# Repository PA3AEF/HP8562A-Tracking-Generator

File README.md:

# Tracking Generator for the HP 8562A/B Spectrum Analyzer  
**Reconstructing the Analyzer’s RF Sweep from Its Local Oscillator**  
**A modular, analyzer‑synchronous architecture**

PA3AEF 2026 

## What this project is

The HP 8562A/B spectrum analyzer does not include a tracking generator.  
However, it exposes enough of its internal LO system to build one externally.

This project implements a **modular, sweep‑synchronous Tracking Generator (TG)** that behaves as if it were a native part of the HP 8562A/B.  
It reconstructs the analyzer’s RF sweep using only:

- 1st LO Output (about 3.9–6.8 GHz)  
- LO Sweep Output (0–10 V, 0.5 V/GHz)  
- 10 MHz reference

The TG becomes a slave to the analyzer’s LO system and rebuilds the RF sweep in real time across multiple microwave bands.

## Why build a Tracking Generator for the HP 8562A/B?

The HP 8562A/B is a legendary instrument: fast, sensitive, and extremely stable.  
But without a tracking generator, it cannot perform:

- filter alignment  
- cavity tuning  
- antenna measurements  
- scalar network analysis  
- frequency response characterization  

This project fills that gap with a TG that follows the analyzer sweep exactly, using the analyzer’s own LO architecture.

## How the analyzer sweeps — and how the TG reconstructs the RF

The HP 8562A/B does not sweep an RF source.  
It sweeps its **first local oscillator** and mixes incoming signals down to a fixed IF.  
To cover 1 kHz–26 GHz, it uses **automatic harmonic mixing**, where each RF band uses a different harmonic of the LO:

| RF Band | Harmonic n | IF | LO Formula |
|--------:|:----------:|----------:|-----------|
| 1 kHz–2.9 GHz | 1 | 3.9107 GHz | LO_SA = RF_SA + 3.9107 GHz |
| 2.75–6.46 GHz | 1 | 310.7 MHz | LO_SA = RF_SA + 0.3107 GHz |
| 5.86–13.0 GHz | 2 | 310.7 MHz | LO_SA = (RF_SA + 0.3107 GHz) / 2 |
| 12.4–19.7 GHz | 3 | 310.7 MHz | LO_SA = (RF_SA + 0.3107 GHz) / 3 |
| 19.1–26.0 GHz | 4 | 310.7 MHz | LO_SA = (RF_SA + 0.3107 GHz) / 4 |

For each band, the analyzer follows: `n * LO_SA = RF_SA + IF`

Because **n changes with band**, the analyzer LO becomes **non‑linear** with respect to the displayed frequency.

A tracking generator must compensate for this non‑linearity to stay aligned.

## How the TG reconstructs the analyzer RF

The TG uses the analyzer LO_SA (or a harmonic of it) as the primary LO and subtracts a fixed IF to recreate the analyzer’s RF:

```
RF_TG = (n * LO_SA) – IF_TG
```

Where:

- IF_TG = 310.7 MHz (fixed for all microwave TG modules)  
- n = analyzer harmonic mode for that band  

This yields:

- Base‑Band (n = 1):  
  RF_TG = LO_SA – 3.9107 GHz

- 6 cm (n = 1):  
  RF_TG = LO_SA – 0.3107 GHz

- 3 cm (n = 2):  
  RF_TG = (2 × LO_SA) – 0.3107 GHz

- 12 mm (n = 4, concept):  
  RF_TG = (4 × LO_SA) – 0.3107 GHz

This architecture reqires **no swept PLLs** in the microwave TG modules.  
Sweep coherence comes entirely from the analyzer LO.

## High‑level TG architecture

The TG system is composed of modular RF boards:

- **MCU board:**  
  Reads sweep voltage, computes RF_SA for calibration, programs PLLs

- **RF SA‑LO Distribution board:**  
  Conditions and splits the analyzer’s 1st LO to all TG modules

- **Base‑Band TG module:**  
  0–2.9 GHz (uses MAX2870)

- **6 cm TG module:**  
  4.4–6.4 GHz (LO_SA direct, IF_TG = 310.7 MHz)

- **3 cm TG module:**  
  9.5–11.5 GHz (LO_SA ×2, IF_TG = 310.7 MHz)

- **12 mm TG module (concept):**  
  22–26 GHz (LO_SA ×4, IF_TG = 310.7 MHz)

Conceptually:

```
Analyzer → LO Distribution → TG Modules → RF Outputs
Analyzer → 10 MHz → PLLs
Analyzer → V_sweep → MCU → Harmonic modules
```

Each TG module reconstructs the analyzer RF at its own band using a mixer‑based architecture.

## TG coverage limits

- **Implemented TG bands:**  
  - Base‑Band (0–2.9 GHz)  
  - 6 cm (4.4–6.4 GHz)  
  - 3 cm (9.5–11.5 GHz)

- **Conceptual / future TG bands:**  
  - 12 mm (22–26 GHz)

- **Analyzer coverage:**  
  - Up to 26 GHz with Option 026  
  - TG coverage currently ends at 11.5 GHz

## Repository structure

```
/docs/architecture
    01-tg-system-architecture.md
    02-lo-architecture.md
    03-analyser-lo-internals.md
    04-rf-sa-lo-distribution.md
    05-baseband-module.md
    06-6cm-module.md
    07-3cm-module.md
    08-12mm-module.md
/docs/architecture/images
    architecture diagrams
/firmware
    MCU firmware (Raspberry Pi Pico)
    overview
    images
/hardware/<module>
    schematics, layouts, BOMs, images
/mechanical
    enclosures, front panels
/usage
    calibration and measurement tools
```

## Status (Oct 19, 2026)

Checkout the [discussion section](https://github.com/PA3AEF/HP8562A-Tracking-Generator/discussions) for updates on the first results I have. 

- File: [example S21 3 cm lossy filter](./images/s21-3cm-lossy-filter.jpg)
- File: [example S11 3 cm pole filter](./images/s11-3cm-pole-filter.jpg)
- MCU board: finshed (I have some boards available) 
- Firmware: finished (Base-band, 6cm and 3cm) 
- LO Distribution: finished 
- Base‑Band module: finished  
- 3 cm module: proof of concept tested OK (tracking at 10 GHz with 2 GHz span)  
- 6 cm module: architecture defined  
- 12 mm module: conceptual design complete  

## License

MIT License.  
See `LICENSE` for details.

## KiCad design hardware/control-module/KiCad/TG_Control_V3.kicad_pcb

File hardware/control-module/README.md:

# Control Module — MCU and 10 MHz Reference Buffer (Hardware)

Compact hardware overview for the Control Module: power sequencing, protection, MCU host interfaces, and the low‑noise 10 MHz reference buffering and 1:4 distribution. Detailed hardware-level descriptions for the **10 MHz reference** and **MCU** are in separate documents (`docs/10MHz_reference.md`, `docs/mcu-hardware.md`). Firmware is covered elsewhere.

## Purpose

- Buffer and distribute an external **10 MHz reference** to **4 isolated outputs**  
- Provide MCU-host hardware: power, programming, debug, and physical control interfaces  
- Protect and condition reference and power inputs (ESD, TVS, reverse polarity)  
- Present SPI/UART/USB headers and status indicators for system integration

## Block Diagram

10 MHz Ref In → Input Protection → Low‑noise Buffer → 1:4 Splitter/Switch → Output Buffers → **4 × SMA REF OUT**  
Power In → Sequencing & Regulators → MCU + Peripherals  
MCU headers: SPI, UART, VRef, Switch, RF-Modules

## Hardware Interfaces

- **Reference Input**
  - **SMA** connector with input protection and level detect
  - DC blocking and optional AC coupling upstream of buffer
- **Reference Outputs**
  - **4 × SMA** buffered outputs, individually enabled
  - Target nominal level: **0 dBm** per output (see `docs/10MHz_reference.md`)
- **Control / Comms**
  - **SPI** header (MOSI, MISO, SCLK, CS, GND, Vcc) for downstream PLLs
  - **UART / USB** hardware interface for firmware connectivity
- **Power**
  - External DC input with reverse‑polarity protection
  - Onboard regulators with power‑good signals and sequencing
- **Indicators**
  - Power, module-select and lock detect fault LEDs at PCB headers

## Design Notes (Hardware Only)

- **Phase noise:** buffer chosen to add minimal phase noise; layout keeps RF ground continuous under RF chain.  
- **Isolation:** per‑output buffering prevents cross‑talk; outputs terminated and DC‑blocked.  
- **Protection:** input ESD, TVS, and surge protection on REF IN and power rails.  
- **Mechanical:** SMA connectors on PCB edge; keep digital switching components physically separated from RF path.  
- **EMC:** ferrite beads, common‑mode chokes, and local decoupling to reduce digital noise coupling into 10 MHz path.  
- **Test points:** RF amplitude, buffer bias, and power‑good nets exposed for bench verification.

## Connector / Pin Summary

- **REF IN:** SMA (10 MHz)  
- **REF OUT 1–4:** SMA buffered outputs  
- **SPI:** 6‑pin header (MOSI, MISO, SCLK, CS, GND, Vcc)  
- **UART/USB:** Micro‑USB or TTL UART header  
- **POWER:** Screw terminal or header;
- **Band Selection:** 3-pin header
- **LO Switch:** 3-pin header
- **RF Modules:** 3-pin and 2-pin headers 

## Control Module

## Documentation

Hardware detail references:  
- **`10MHz_reference.md`** — full schematic, BOM, and RF measurements  
- **`mcu-hardware.md`** — MCU pinout, power sequencing, and debug connectors  
- **`control-module`** — mechanical drawings and test fixtures

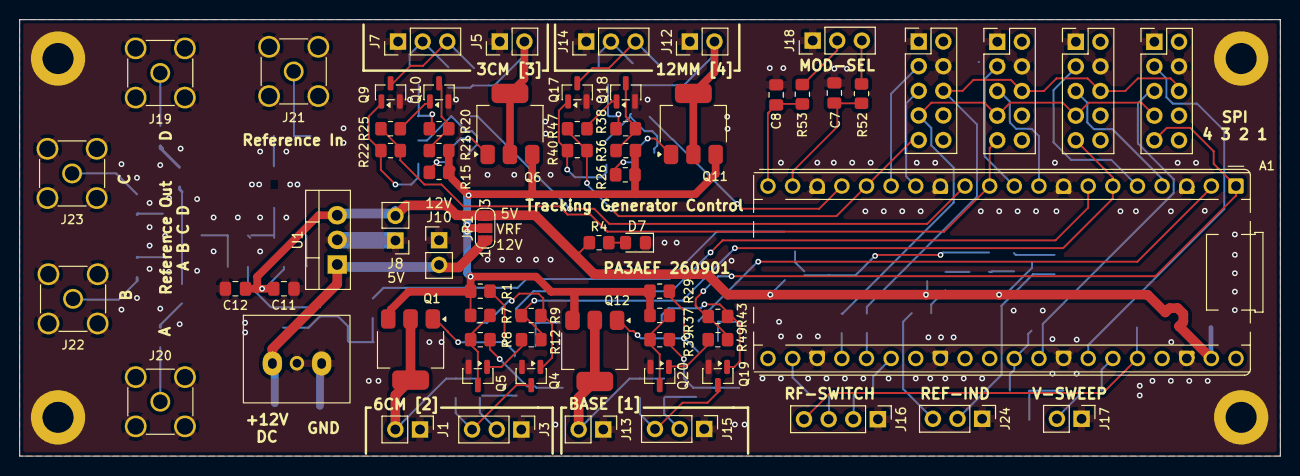
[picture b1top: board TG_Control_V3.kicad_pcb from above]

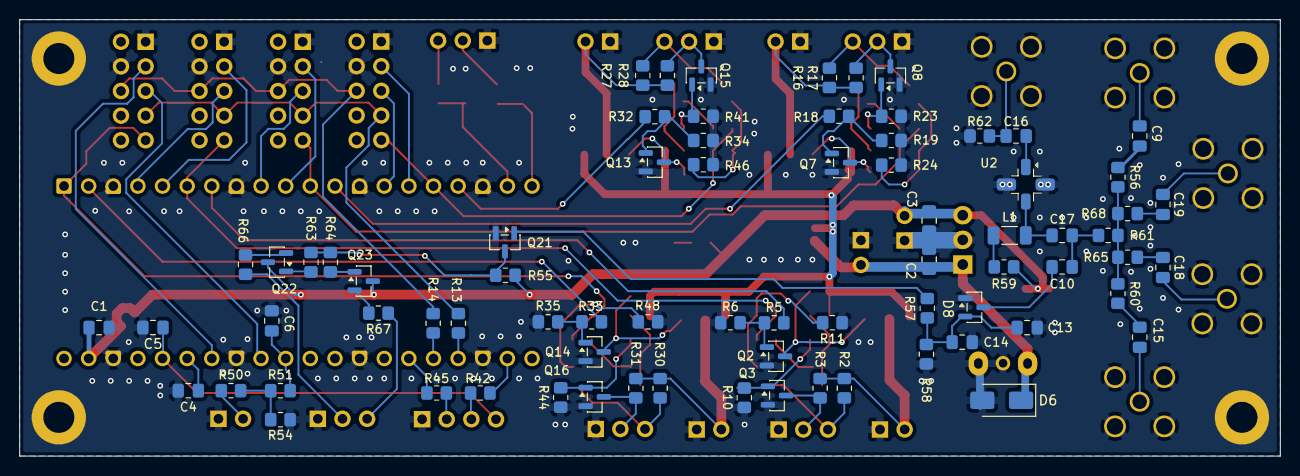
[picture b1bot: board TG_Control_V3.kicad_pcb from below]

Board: 2 copper layers, 130.0 x 45.0 mm, 146 parts (75 on the bottom side), 98 nets.

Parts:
A1: RaspberryPi_Pico; RaspberryPi_Pico_Common_THT
C1, C3, C4, C5, C6, C7, C8, C9, C11, C15, C16, C17, C18, C19: 100nF; C_0805_2012Metric_Pad1.18x1.45mm_HandSolder
C2: 330nF; C_0805_2012Metric_Pad1.18x1.45mm_HandSolder
C10: 1pF; C_0805_2012Metric_Pad1.18x1.45mm_HandSolder
C12: 10uF; C_0805_2012Metric_Pad1.18x1.45mm_HandSolder
C13: 1nF; C_0805_2012Metric_Pad1.18x1.45mm_HandSolder
C14: 47uF; C_0805_2012Metric_Pad1.18x1.45mm_HandSolder
D6: 1N4001; D_SMA
D7: LED; LED_0805_2012Metric_Pad1.15x1.40mm_HandSolder
D8: BAT54S; SOT-23
H1, H2, H3, H4: MountingHole_Pad; MountingHole_3.2mm_M3_DIN965_Pad
J1, J5, J8, J10, J12, J13, J17: Conn_01x02; PinHeader_1x02_P2.54mm_Vertical
J2: SCREW_TERMINAL; Screw terminal 3 pin
J3, J7, J14, J15, J18, J24: Conn_01x03; PinHeader_1x03_P2.54mm_Vertical
J4, J6, J9, J11: Conn_02x05_Odd_Even; PinHeader_2x05_P2.54mm_Vertical
J16: Conn_01x04; PinHeader_1x04_P2.54mm_Vertical
J19, J20, J21, J22, J23: Conn_Coaxial; SMA_Amphenol_901-144_Vertical
JP1: SolderJumper_3_Open; SolderJumper-3_P1.3mm_Open_RoundedPad1.0x1.5mm_NumberLabels
L1: 22nH; L_1206_3216Metric_Pad1.22x1.90mm_HandSolder
Q1, Q6, Q11, Q12: ZXMP4A16G; SOT-223-3_TabPin2
Q2, Q3, Q4, Q5, Q7, Q8, Q9, Q10, Q13, Q14, Q15, Q16, Q17, Q18, Q19, Q20, Q23: MMBTA14; SOT-23
Q21: MMBT3904; SOT-23
Q22: BC857; SOT-23
R1, R5, R8, R9, R12, R15, R18, R21, R22, R25, R26, R29, R32, R33, R38, R39, R40, R43, R47, R49, R54, R63, R64: 10K; R_0805_2012Metric_Pad1.20x1.40mm_HandSolder
R2, R3, R16, R17, R27, R28, R30, R31: **; R_0805_2012Metric_Pad1.20x1.40mm_HandSolder
R4, R66, R67: 3K3; R_0805_2012Metric_Pad1.20x1.40mm_HandSolder
R6, R10, R11, R19, R23, R24, R34, R35, R41, R44, R46, R48: 100K; R_0805_2012Metric_Pad1.20x1.40mm_HandSolder
R7, R20, R36, R37: 68K; R_0805_2012Metric_Pad1.20x1.40mm_HandSolder
R13, R14: 0R; R_0805_2012Metric_Pad1.20x1.40mm_HandSolder
R42, R45, R52, R53: 100R; R_0805_2012Metric_Pad1.20x1.40mm_HandSolder
R50: 22K; R_0805_2012Metric_Pad1.20x1.40mm_HandSolder
R51: 1K; R_0805_2012Metric_Pad1.20x1.40mm_HandSolder
R55: 3k3; R_0805_2012Metric_Pad1.20x1.40mm_HandSolder
R56, R60, R61, R65, R68: 39R; R_0805_2012Metric_Pad1.20x1.40mm_HandSolder
R57: 8k2; R_0805_2012Metric_Pad1.20x1.40mm_HandSolder
R58: 47K; R_0805_2012Metric_Pad1.20x1.40mm_HandSolder
R59: 33R; R_0805_2012Metric_Pad1.20x1.40mm_HandSolder
R62: 49R9; R_0805_2012Metric_Pad1.20x1.40mm_HandSolder
U1: LM7805_TO220; TO-220-3_Vertical
U2: MAR-6+; MSA_1

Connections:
+3V3: A1.36 (3V3), C5.1, J16.4
+5V: A1.39 (VSYS), C1.2, C3.1, C11.2, C12.2, J8.2, JP1.3 (B), Q22.3 (C), Q23.3 (C), R4.1, R55.1, R59.2, U1.3 (VO)
+12V: C2.1, D6.1 (K), J2.1, J10.2, JP1.1 (A), U1.1 (VI)
/10 MHz Reference/REF-DETECT: J24.2, R66.2
/10 MHz Reference/REF-DETECT-N: J24.3, R67.1
/10 MHz Reference/REF_DET_N: Q21.3 (C), R55.2, R63.1, R64.1
/10 MHz Reference/REF_PRESENT: C10.1, C17.2, R61.1
/MCU/CE_3CM: A1.10 (GPIO7), J9.3
/MCU/CE_6CM: A1.5 (GPIO3), J6.3
/MCU/CE_12MM: A1.15 (GPIO11), J11.3
/MCU/CE_BASE: A1.34 (GPIO28_ADC2), J4.3
/MCU/CS_3CM: A1.9 (GPIO6), J9.5
/MCU/CS_6CM: A1.4 (GPIO2), J6.5
/MCU/CS_12MM: A1.14 (GPIO10), J11.5
/MCU/CS_BASE: A1.32 (GPIO27_ADC1), J4.5
/MCU/LD-3CM-GN: J7.2, Q8.3 (C), R17.2
/MCU/LD-3CM-RD: J7.3, Q9.3 (C), R16.1
/MCU/LD-6CM-GN: J3.2, Q3.3 (C), R3.2
/MCU/LD-6CM-RD: J3.3, Q4.3 (C), R2.1
/MCU/LD-12MM-GN: J14.2, Q15.3 (C), R28.2
/MCU/LD-12MM-RD: J14.3, Q17.3 (C), R27.1
/MCU/LD-BASE-GN: J15.2, Q16.3 (C), R31.2
/MCU/LD-BASE-RD: J15.3, Q19.3 (C), R30.1
/MCU/LD_3CM: A1.11 (GPIO8), J9.9, R22.1, R25.1
/MCU/LD_6CM: A1.6 (GPIO4), J6.9, R9.1, R12.1
/MCU/LD_12MM: A1.16 (GPIO12), J11.9, R40.1, R47.1
/MCU/LD_BASE: A1.1 (GPIO0), J4.9, R43.1, R49.2
/MCU/MOD-SEL1: J18.2, R53.1
/MCU/MOD-SEL2: J18.3, R52.1
/MCU/MOSI: J4.6, J6.6, J9.6, J11.6, R14.2
/MCU/PE_A: A1.26 (GPIO20), R45.2
/MCU/PE_B: A1.22 (GPIO17), R42.2
/MCU/RF-3CM-PWR: J5.2, Q6.2 (D), R16.2, R17.1
/MCU/RF-6CM-PWR: J1.2, Q1.2 (D), R2.2, R3.1
/MCU/RF-12MM-PWR: J12.2, Q11.2 (D), R27.2, R28.1
/MCU/RF-BASE-PWR: J13.2, Q12.2 (D), R30.2, R31.1
/MCU/RFEN_3CM: A1.12 (GPIO9), R18.1
/MCU/RFEN_6CM: A1.7 (GPIO5), R5.1
/MCU/RFEN_12MM: A1.17 (GPIO13), R32.1
/MCU/RFEN_BASE: A1.2 (GPIO1), R33.1
/MCU/RFSW-A: J16.2, R45.1
/MCU/RFSW-B: J16.3, R42.1
/MCU/ROT_A: A1.19 (GPIO14), C7.1, R52.2
/MCU/ROT_B: A1.20 (GPIO15), C8.1, R53.2
/MCU/SCK: J4.7, J6.7, J9.7, J11.7, R13.2
/MCU/V_RF: JP1.2 (C), Q1.3 (S), Q6.3 (S), Q11.3 (S), Q12.3 (S), R1.1, R7.2, R15.1, R20.2, R26.1, R29.1, R36.2, R37.2
/MCU/Vsense: A1.31 (GPIO26_ADC0), C6.1, R51.2
GND: A1.3 (GND), A1.8 (GND), A1.13 (GND), A1.18 (GND), A1.23 (GND), A1.28 (GND), A1.33 (AGND), A1.38 (GND), C1.1, C2.2, C3.2, C4.2, C5.2, C6.2, C7.2, C8.2, C11.1, C12.1, C13.1, C14.1, D6.2 (A), D7.1 (K), D8.1 (A), H1.1 (1_1), H2.1 (1_1), H3.1 (1_1), H4.1 (1_1), J1.1, J2.2, J3.1, J4.1, J4.4, J5.1, J6.1, J6.4, J7.1, J8.1, J9.1, J9.4, J10.1, J11.1, J11.4, J12.1, J13.1, J14.1, J15.1, J16.1, J17.1, J18.1, J19.2 (Ext), J20.2 (Ext), J21.2 (Ext), J22.2 (Ext), J23.2 (Ext), J24.1, Q2.2 (E), Q3.2 (E), Q4.2 (E), Q5.2 (E), Q7.2 (E), Q8.2 (E), Q9.2 (E), Q10.2 (E), Q13.2 (E), Q14.2 (E), Q15.2 (E), Q16.2 (E), Q17.2 (E), Q18.2 (E), Q19.2 (E), Q20.2 (E), Q21.2 (E), R6.1, R10.1, R11.1, R19.1, R23.1, R24.1, R34.1, R35.1, R41.1, R44.1, R46.1, R48.1, R54.2, R58.2, R62.2, U1.2 (GND), U2.3 (GND), U2.4 (GND)
unnamed: A1.35 (ADC_VREF), C4.1
unnamed: A1.24 (GPIO18), R13.1
unnamed: A1.25 (GPIO19), R14.1
unnamed: C9.1, R56.2
unnamed: C15.1, R60.2
unnamed: C18.1, R65.2
unnamed: C19.1, R68.2
unnamed: D7.2 (A), R4.2
unnamed: C10.2, D8.3 (COM)
unnamed: C13.2, C14.2, D8.2 (K), R57.1, R58.1
unnamed: J17.2, R50.1
unnamed: C9.2, J19.1 (In)
unnamed: C15.2, J20.1 (In)
unnamed: C16.1, J21.1 (In), R62.1
unnamed: C18.2, J22.1 (In)
unnamed: C19.2, J23.1 (In)
unnamed: L1.1, R59.1
unnamed: Q1.1 (G), Q2.3 (C), R1.2
unnamed: Q2.1 (B), R5.2, R6.2
unnamed: Q3.1 (B), R8.2, R10.2
unnamed: Q4.1 (B), R9.2, R11.2
unnamed: Q5.1 (B), R12.2
unnamed: Q5.3 (C), R7.1, R8.1
unnamed: Q6.1 (G), Q7.3 (C), R15.2
unnamed: Q7.1 (B), R18.2, R19.2
unnamed: Q8.1 (B), R21.2, R23.2
unnamed: Q9.1 (B), R22.2, R24.2
unnamed: Q10.1 (B), R25.2
unnamed: Q10.3 (C), R20.1, R21.1
unnamed: Q11.1 (G), Q13.3 (C), R26.2
unnamed: Q12.1 (G), Q14.3 (C), R29.2
unnamed: Q13.1 (B), R32.2, R34.2
unnamed: Q14.1 (B), R33.2, R35.2
unnamed: Q15.1 (B), R38.2, R41.2
unnamed: Q16.1 (B), R39.2, R44.2
unnamed: Q17.1 (B), R40.2, R46.2
unnamed: Q18.1 (B), R47.2
unnamed: Q18.3 (C), R36.1, R38.1
unnamed: Q19.1 (B), R43.2, R48.2
unnamed: Q20.1 (B), R49.1
unnamed: Q20.3 (C), R37.1, R39.1
unnamed: Q21.1 (B), R57.2
unnamed: Q22.1 (B), R63.2
unnamed: Q22.2 (E), R66.1
unnamed: Q23.1 (B), R64.2
unnamed: Q23.2 (E), R67.2
unnamed: R50.2, R51.1, R54.1
unnamed: R56.1, R60.1, R61.2, R65.1, R68.1
unnamed: C16.2, U2.1 (IN)
unnamed: C17.1, L1.2, U2.2 (OUT)

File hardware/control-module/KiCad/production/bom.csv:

Designator,Footprint,Quantity,Value,LCSC Part #
A1,RaspberryPi_Pico_Common_THT,1,RaspberryPi_Pico,
"C1, C11, C15, C16, C17, C18, C19, C3, C4, C5, C6, C7, C8, C9",0805,14,100nF,
C10,0805,1,1pF,
C12,0805,1,10uF,
C13,0805,1,1nF,
C14,0805,1,47uF,
C2,0805,1,330nF,
D6,D_SMA,1,1N4001,
D7,0805,1,LED,
D8,SOT-23,1,BAT54S,
"J1, J10, J12, J13, J5, J8",PinHeader_1x02_P2.54mm_Vertical,6,Conn_01x02,
"J11, J4, J6, J9",PinHeader_2x05_P2.54mm_Vertical,4,Conn_02x05_Odd_Even,
"J14, J15, J18, J24, J3, J7",PinHeader_1x03_P2.54mm_Vertical,6,Conn_01x03,
J16,PinHeader_1x04_P2.54mm_Vertical,1,Conn_01x04,
"J19, J20, J21, J22, J23",SMA_Amphenol_901-144_Vertical,5,Conn_Coaxial,
J2,Screw terminal 3 pin,1,SCREW_TERMINAL,
L1,1206,1,22nH,
"Q1, Q11, Q12, Q6",SOT-223-3_TabPin2,4,ZXMP4A16G,
"Q10, Q13, Q14, Q15, Q16, Q17, Q18, Q19, Q2, Q20, Q23, Q3, Q4, Q5, Q7, Q8, Q9",SOT-23,17,MMBTA14,
Q21,SOT-23,1,MMBT3904,
Q22,SOT-23,1,BC857,
"R1, R12, R15, R18, R21, R22, R25, R26, R29, R32, R33, R38, R39, R40, R43, R47, R49, R5, R63, R64, R8, R9",0805,22,10K,
"R10, R11, R19, R23, R24, R34, R35, R41, R44, R46, R48, R6",0805,12,100K,
"R13, R14",0805,2,0R,
"R16, R17, R2, R27, R28, R3, R30, R31",0805,8,**,
"R20, R36, R37, R7",0805,4,68K,
"R4, R55, R66, R67",0805,4,3K3,
"R42, R45, R52, R53",0805,4,100R,
"R56, R60, R61, R65, R68",0805,5,39R,
R57,0805,1,8k2,
R58,0805,1,47K,
R59,0805,1,33R,
R62,0805,1,49R9,
U1,TO-220-3_Vertical,1,LM7805_TO220,
U2,MSA_1,1,MAR-6+,

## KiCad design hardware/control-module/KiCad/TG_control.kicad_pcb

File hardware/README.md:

# Hardware — TG Project

This directory contains all hardware designs for the modular Tracking Generator (TG).  
Each RF module is fully self‑contained with its own schematic, PCB if applicable, and data on on read-made building-blocks.

The hardware is organized into four primary modules:

- **Baseband Module (0–2.9 GHz)**
- **6 cm Module (4.4–6.4 GHz)**
- **3 cm Module (8.5–11.5 GHz)**
- **LO Module (Isolation and distribution of 1st LO from SA)**

All PCBs are designed in KiCad and stored in separate subdirectories.

## Directory Structure

Each module directory contains:

- **`schematic.pdf`** — complete schematic  
- **`pcb/`** — KiCad PCB files, 3D views, fabrication output  
- **`bom.csv`** — Bill of Materials  
- **`readme.md`** — module‑specific documentation (gain budget, design notes, test plan)

## Hardware Module Overview

### **Baseband Module (0–2.9 GHz)**
- IF chain from the HMC219 downconverter
- PLL at 3.9107 GHz  
- 3 GHz low‑pass filter  
- Pads, IF amplifier, SMA output  

### **6 cm Module (4.4–6.4 GHz)**
- HMC220 mixer  
- IF and RF amplification  
- Band‑pass filtering for 4–8 GHz  
- Purpose: upconversion for the 6 cm tracking generator band

### **3 cm Module (9.5–11.5 GHz)**
- HMC220 mixer 
- PLL at 310.7 MHz
- Band-pass filter at 310 MHz 
- High‑frequency RF amplifier (9–12 GHz)  
- Band‑pass filtering for 8–12 GHz  
- Purpose: upconversion for the 3 cm tracking generator band

### **Control Module**
- Raspberry Pi microcontroller
- Control of all circuitry, indicators, etc.
- Power provision for each band module (5-12V selectable) 
- Prper startup-shutdown sequence for band switching
- 10 MHz reference input buffering and distribution (SMA)
- SPI control for PLLs 

### **LO Module**
- Isolation of 1st LO output of analyser
- Braodband amplification of 1st LO output
- Distribution of 1st LO to band modules 

## Design Principles

- **Modular:** each RF module is electrically and mechanically independent  
- **SMA‑based:** all interconnects use SMA cables for clean, predictable RF paths  
- **Reproducible:** BOMs, schematics, and PCB files are fully documented  
- **RF‑optimized:** short signal paths, solid grounding, controlled impedance  
- **Measurable:** each module includes clear test points and a documented gain budget

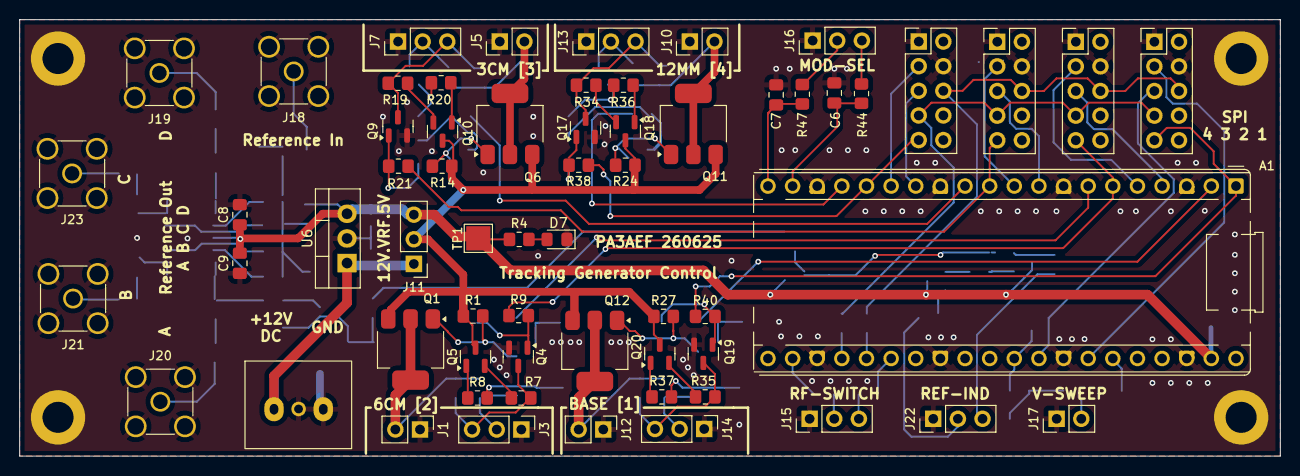
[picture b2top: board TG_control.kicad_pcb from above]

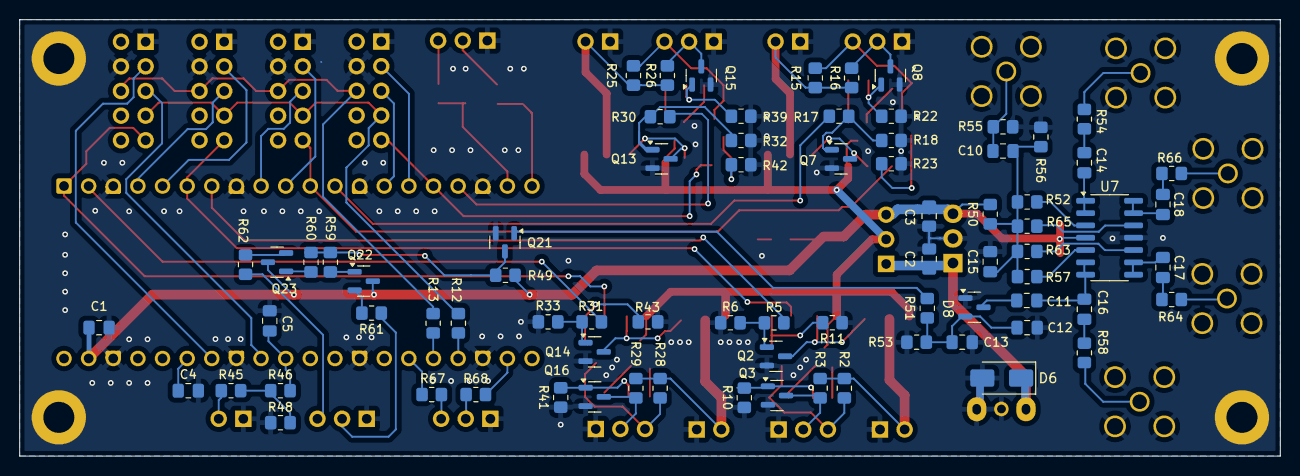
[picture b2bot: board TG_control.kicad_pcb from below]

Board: 2 copper layers, 130.0 x 45.0 mm, 143 parts (77 on the bottom side), 101 nets.

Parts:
A1: RaspberryPi_Pico; RaspberryPi_Pico_Common_THT
C1, C3, C4, C5, C6, C7, C9, C10, C14, C16, C17, C18: 100nF; C_0805_2012Metric_Pad1.18x1.45mm_HandSolder
C2: 330nF; C_0805_2012Metric_Pad1.18x1.45mm_HandSolder
C8: 10uF; C_0805_2012Metric_Pad1.18x1.45mm_HandSolder
C11: 1pF; C_0805_2012Metric_Pad1.18x1.45mm_HandSolder
C12: 1nF; C_0805_2012Metric_Pad1.18x1.45mm_HandSolder
C13: 22uF; C_0805_2012Metric_Pad1.18x1.45mm_HandSolder
C15: 1uF; C_0805_2012Metric_Pad1.18x1.45mm_HandSolder
D6: 1N4001; D_SMA
D7: LED; LED_0805_2012Metric_Pad1.15x1.40mm_HandSolder
D8: BAT54S; SOT-23
H1, H2, H3, H4: MountingHole_Pad; MountingHole_3.2mm_M3_DIN965_Pad
J1, J5, J10, J12, J17: Conn_01x02; PinHeader_1x02_P2.54mm_Vertical
J2: SCREW_TERMINAL; Screw terminal 3 pin
J3, J7, J11, J13, J14, J15, J16, J22: Conn_01x03; PinHeader_1x03_P2.54mm_Vertical
J4, J6, J8, J9: Conn_02x05_Odd_Even; PinHeader_2x05_P2.54mm_Vertical
J18, J19, J20, J21, J23: Conn_Coaxial; SMA_Amphenol_901-144_Vertical
Q1, Q6, Q11, Q12: ZXMP4A16G; SOT-223-3_TabPin2
Q2, Q3, Q4, Q7, Q8, Q9, Q13, Q14, Q15, Q16, Q17, Q19, Q21, Q22: MMBTA14; SOT-23
Q5, Q10, Q18, Q20: BC857C; SOT-23
Q23: BC857; SOT-23
R1, R5, R7, R8, R9, R14, R17, R19, R20, R21, R24, R27, R30, R31, R34, R35, R36, R37, R38, R40, R48, R50, R56, R59, R60: 10K; R_0805_2012Metric_Pad1.20x1.40mm_HandSolder
R2, R3, R15, R16, R25, R26, R28, R29: **; R_0805_2012Metric_Pad1.20x1.40mm_HandSolder
R4, R61, R62: 3K3; R_0805_2012Metric_Pad1.20x1.40mm_HandSolder
R6, R10, R11, R18, R22, R23, R32, R33, R39, R41, R42, R43: 100K; R_0805_2012Metric_Pad1.20x1.40mm_HandSolder
R12, R13: 0R; R_0805_2012Metric_Pad1.20x1.40mm_HandSolder
R44, R47, R52, R57, R63, R65, R67, R68: 100R; R_0805_2012Metric_Pad1.20x1.40mm_HandSolder
R45: 22K; R_0805_2012Metric_Pad1.20x1.40mm_HandSolder
R46: 1K; R_0805_2012Metric_Pad1.20x1.40mm_HandSolder
R49: 3k3; R_0805_2012Metric_Pad1.20x1.40mm_HandSolder
R51: 8k2; R_0805_2012Metric_Pad1.20x1.40mm_HandSolder
R53: 47K; R_0805_2012Metric_Pad1.20x1.40mm_HandSolder
R54, R55, R58, R64, R66: 49R9; R_0805_2012Metric_Pad1.20x1.40mm_HandSolder
TP1: 5V; TestPoint_Pad_2.5x2.5mm
U6: LM7805_TO220; TO-220-3_Vertical
U7: OPA1679; SOIC-14_3.9x8.7mm_P1.27mm

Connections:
+5V: A1.39 (VSYS), C1.2, C3.1, C8.2, C9.2, J11.3, Q22.3 (C), Q23.3 (C), R4.1, R49.1, R50.1, TP1.1, U6.3 (VO), U7.4 (V+)
+12V: C2.1, D6.1 (K), J2.1, J11.1, U6.1 (VI)
/10 MHz Reference/REF-DETECT: J22.3, R62.2
/10 MHz Reference/REF-DETECT-N: J22.2, R61.1
/10 MHz Reference/REF_DET_N: Q21.3 (C), R49.2, R59.1, R60.1
/10 MHz Reference/REF_PRESENT: C11.1, C16.1, U7.6 (-), U7.7
/MCU/CE_3CM: A1.10 (GPIO7), J8.3
/MCU/CE_6CM: A1.5 (GPIO3), J6.3
/MCU/CE_12MM: A1.15 (GPIO11), J9.3
/MCU/CE_BASE: A1.34 (GPIO28_ADC2), J4.3
/MCU/CS_3CM: A1.9 (GPIO6), J8.5
/MCU/CS_6CM: A1.4 (GPIO2), J6.5
/MCU/CS_12MM: A1.14 (GPIO10), J9.5
/MCU/CS_BASE: A1.32 (GPIO27_ADC1), J4.5
/MCU/LD-3CM-GN: J7.2, Q8.3 (C), R16.2
/MCU/LD-3CM-RD: J7.3, Q9.3 (C), R15.1, R19.2
/MCU/LD-6CM-GN: J3.2, Q3.3 (C), R3.2
/MCU/LD-6CM-RD: J3.3, Q4.3 (C), R2.1, R7.2
/MCU/LD-12MM-GN: J13.2, Q15.3 (C), R26.2
/MCU/LD-12MM-RD: J13.3, Q17.3 (C), R25.1, R34.2
/MCU/LD-BASE-GN: J14.2, Q16.3 (C), R29.2
/MCU/LD-BASE-RD: J14.3, Q19.3 (C), R28.1, R35.1
/MCU/LD_3CM: A1.11 (GPIO8), J8.9, R21.1
/MCU/LD_6CM: A1.6 (GPIO4), J6.9, R9.1
/MCU/LD_12MM: A1.16 (GPIO12), J9.9, R38.1
/MCU/LD_BASE: A1.1 (GPIO0), J4.9, R40.1
/MCU/MOD-SEL1: J16.2, R47.1
/MCU/MOD-SEL2: J16.3, R44.1
/MCU/MOSI: J4.6, J6.6, J8.6, J9.6, R13.2
/MCU/PE_A: A1.26 (GPIO20), R67.2
/MCU/PE_B: A1.22 (GPIO17), R68.2
/MCU/RF-3CM-PWR: J5.2, Q6.2 (D), R15.2, R16.1
/MCU/RF-6CM-PWR: J1.2, Q1.2 (D), R2.2, R3.1
/MCU/RF-12MM-PWR: J10.2, Q11.2 (D), R25.2, R26.1
/MCU/RF-BASE-PWR: J12.2, Q12.2 (D), R28.2, R29.1
/MCU/RFEN_3CM: A1.12 (GPIO9), R17.1
/MCU/RFEN_6CM: A1.7 (GPIO5), R5.1
/MCU/RFEN_12MM: A1.17 (GPIO13), R30.1
/MCU/RFEN_BASE: A1.2 (GPIO1), R31.1
/MCU/RFSW-A: J15.3, R67.1
/MCU/RFSW-B: J15.2, R68.1
/MCU/ROT_A: A1.19 (GPIO14), C6.1, R44.2
/MCU/ROT_B: A1.20 (GPIO15), C7.1, R47.2
/MCU/SCK: J4.7, J6.7, J8.7, J9.7, R12.2
/MCU/V_RF: J11.2, Q1.3 (S), Q5.3 (E), Q6.3 (S), Q10.3 (E), Q11.3 (S), Q12.3 (S), Q18.3 (E), Q20.3 (E), R1.1, R14.1, R24.1, R27.1
/MCU/Vref: A1.35 (ADC_VREF), C4.1
/MCU/Vsense: A1.31 (GPIO26_ADC0), C5.1, R46.2
GND: A1.3 (GND), A1.8 (GND), A1.13 (GND), A1.18 (GND), A1.23 (GND), A1.28 (GND), A1.33 (AGND), A1.38 (GND), C1.1, C2.2, C3.2, C4.2, C5.2, C6.2, C7.2, C8.1, C9.1, C12.1, C13.1, C15.1, D6.2 (A), D7.1 (K), D8.1 (A), H1.1, H2.1, H3.1, H4.1, J1.1, J2.2, J3.1, J4.1, J4.4, J5.1, J6.1, J6.4, J7.1, J8.1, J8.4, J9.1, J9.4, J10.1, J12.1, J13.1, J14.1, J15.1, J16.1, J17.1, J18.2 (Ext), J19.2 (Ext), J20.2 (Ext), J21.2 (Ext), J22.1, J23.2 (Ext), Q2.2 (E), Q3.2 (E), Q4.2 (E), Q7.2 (E), Q8.2 (E), Q9.2 (E), Q13.2 (E), Q14.2 (E), Q15.2 (E), Q16.2 (E), Q17.2 (E), Q19.2 (E), Q21.2 (E), R6.1, R10.1, R11.1, R18.1, R22.1, R23.1, R32.1, R33.1, R39.1, R41.1, R42.1, R43.1, R48.2, R53.2, R55.2, R56.2, U6.2 (GND), U7.11 (V-)
unnamed: A1.24 (GPIO18), R12.1
unnamed: A1.25 (GPIO19), R13.1
unnamed: C10.2, C15.2, R50.2, R52.1, R56.1, R57.1, R63.1, R65.1
unnamed: C14.2, R54.1
unnamed: C16.2, R58.1
unnamed: C17.2, R64.1
unnamed: C18.2, R66.2
unnamed: D7.2 (A), R4.2
unnamed: C11.2, D8.3 (COM)
unnamed: C12.2, C13.2, D8.2 (K), R51.1, R53.1
unnamed: J17.2, R45.1
unnamed: C10.1, J18.1 (In), R55.1
unnamed: J19.1 (In), R54.2
unnamed: J20.1 (In), R58.2
unnamed: J21.1 (In), R64.2
unnamed: J23.1 (In), R66.1
unnamed: Q1.1 (G), Q2.3 (C), R1.2
unnamed: Q2.1 (B), R5.2, R6.2
unnamed: Q3.1 (B), R8.2, R10.2
unnamed: Q4.1 (B), R9.2, R11.2
unnamed: Q5.2 (B), R7.1
unnamed: Q5.1 (C), R8.1
unnamed: Q6.1 (G), Q7.3 (C), R14.2
unnamed: Q7.1 (B), R17.2, R18.2
unnamed: Q8.1 (B), R20.2, R22.2
unnamed: Q9.1 (B), R21.2, R23.2
unnamed: Q10.2 (B), R19.1
unnamed: Q10.1 (C), R20.1
unnamed: Q11.1 (G), Q13.3 (C), R24.2
unnamed: Q12.1 (G), Q14.3 (C), R27.2
unnamed: Q13.1 (B), R30.2, R32.2
unnamed: Q14.1 (B), R31.2, R33.2
unnamed: Q15.1 (B), R36.2, R39.2
unnamed: Q16.1 (B), R37.2, R41.2
unnamed: Q17.1 (B), R38.2, R42.2
unnamed: Q18.2 (B), R34.1
unnamed: Q18.1 (C), R36.1
unnamed: Q19.1 (B), R40.2, R43.2
unnamed: Q20.2 (B), R35.2
unnamed: Q20.1 (C), R37.1
unnamed: Q21.1 (B), R51.2
unnamed: Q22.1 (B), R59.2
unnamed: Q22.2 (E), R61.2
unnamed: Q23.1 (B), R60.2
unnamed: Q23.2 (E), R62.1
unnamed: R45.2, R46.1, R48.1
unnamed: R52.2, U7.3 (+)
unnamed: C14.1, U7.1, U7.2 (-)
unnamed: R57.2, U7.5 (+)
unnamed: R63.2, U7.10 (+)
unnamed: C17.1, U7.8, U7.9 (-)
unnamed: R65.2, U7.12 (+)
unnamed: C18.1, U7.13 (-), U7.14

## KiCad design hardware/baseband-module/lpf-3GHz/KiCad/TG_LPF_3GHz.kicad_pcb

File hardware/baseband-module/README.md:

# Base‑Band Tracking Generator Module  
**(0–2.9 GHz fundamental‑mode section)**

The Base‑Band module generates the 0–2.9 GHz portion of the Tracking Generator output.  
It uses the analyzer’s 1st LO as the swept RF input and mixes it with a locally generated LO_TG to recreate the analyzer’s RF sweep at the TG output.

This module contains the **core RF building blocks** for fundamental‑mode operation:

- clean LO_TG generation  
- LO driver amplification  
- fundamental mixer  
- post‑mix filtering  
- output leveling  

All signals remain coherent with the analyzer because the MAX2870 locks to the analyzer’s 10 MHz reference.

---

## Module Overview

The Base‑Band module consists of the following RF chain:

1. **Analyzer 1st LO input from the LO Distribution module**  
2. **MAX2870 PLL generating LO_TG (fixed 3.9107 GHz)**  
3. **LO driver amplifier (20 dB gain)**  
4. **LO band‑pass filter + pad**  
5. **Fundamental mixer (HMC219)**  
6. **Low‑pass filter (DC–3 GHz)**  
7. **Output pad (level trim)**

Each block is described below.

---

## Building Blocks (LO_TG path)

### MAX2870 PLL / LO_TG Source
- Generates the fixed LO_TG required for fundamental mixing.  
- Locked to the analyzer’s 10 MHz reference for coherence.  
- Output level is low (programmable -4 dBm to +5 dBm) and requires external amplification.  
- Ready‑made MAX2870 modules with SPI and SMA connectors work well

---

### LO Driver Amplifier (3.9 GHz)
- Raises the MAX2870 output to proper mixer‑drive levels.  
- Provides stable gain and low added phase noise.  
- Offers isolation between the PLL and the mixer LO port.  
- A boxed 20 dB gain module with SMA I/O is ideal.

---

### LO Band‑Pass Filter (3.9107 GHz) + Pad
- Cleans up PLL and amplifier spurs.  
- Ensures a spectrally clean LO_TG at the mixer.  
- Final pad sets the LO level to ~13 dBm at the HMC219 LO pin.  
- Ready‑made BPF modules with SMA I/O work well, but DIY can perform equally well

---

## Mixer and Output Path

### Fundamental Mixer (HMC219)
- Core element of the Base‑Band module.  
- RF port: analyzer 1st LO (3.9–6.8 GHz)  
- LO port: LO_TG (~13 dBm)  
- IF/RF output: 0–2.9 GHz TG signal  
- Requires good grounding and shielding to minimize LO feedthrough.  
- Ready‑made boxed modules very much simplify construction.\

### Low‑Pass Filter (DC–3 GHz)
- Removes mixer images and LO leakage.  
- Defines the usable Base‑Band TG output range.  
- Should have low insertion loss and strong stop‑band rejection.  
- DIY CNC‑boxed LPF is fine; ready‑made modules also work.
- Optional pad trims the output to 0 dBm.

**HFSS modeling results optimized for standard LC values:**

Another solution was modeled using folded stepped impedance open subs after Makki et al. 

## Performance Goals

### Frequency Tracking
- Output range: 0–2.9 GHz  
- Must follow analyzer sweep exactly  
- Settling must match analyzer sweep speed

### Amplitude Performance
- Target output: ~0 dBm  
- Flatness corrected at system level  
- Avoid compression in the LO driver and mixer

### Spectral Cleanliness
- Low LO leakage  
- Low mixer images  
- Spurs dominated by PLL  
- Phase noise dominated by analyzer LO

### Implementation Notes
- RF‑clean routing up to 3 GHz  
- Strong isolation between LO_TG and RF paths  

## Summary

The Base‑Band module is straightforward once broken into functional blocks.  
Each block (PLL, LO driver, mixer, filters, pads) can be built and tested independently.
Many blocks are ready-made available.

---

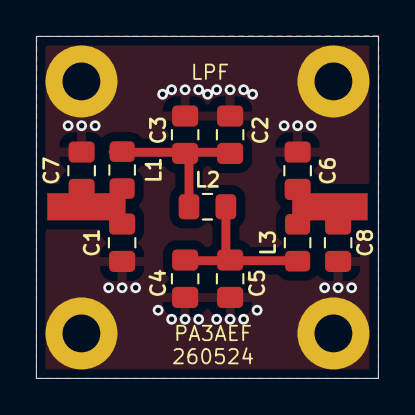
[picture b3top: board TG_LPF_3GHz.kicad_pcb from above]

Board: 2 copper layers, 19.0 x 19.0 mm, 15 parts (0 on the bottom side), 5 nets.

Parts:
C1, C2, C3, C4, C5, C6: 1pF; C_0805_2012Metric_Pad1.18x1.45mm_HandSolder
C7, C8: 0pF; C_0805_2012Metric_Pad1.18x1.45mm_HandSolder
H1, H2, H3, H4: Hole_M2; MountingHole_2.1mm_M2_Pad
L1, L3: 3n9; L_0805_2012Metric_Pad1.15x1.40mm_HandSolder
L2: 4n7; L_0805_2012Metric_Pad1.15x1.40mm_HandSolder

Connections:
GND: C1.1, C2.1, C3.1, C4.1, C5.1, C6.1, C7.2, C8.2, H1.1, H2.1, H3.1, H4.1
unnamed: C1.2, C7.1, L1.1
unnamed: C2.2, C3.2, L1.2, L2.1
unnamed: C4.2, C5.2, L2.2, L3.1
unnamed: C6.2, C8.1, L3.2

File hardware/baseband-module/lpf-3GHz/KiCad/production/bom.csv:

Designator,Footprint,Quantity,Value,LCSC Part #
"C1, C2, C3, C4, C5, C6",0805,6,1pF,
"C7, C8",0805,2,0pF,
"L1, L3",0805,2,3n9,
L2,0805,1,4n7,

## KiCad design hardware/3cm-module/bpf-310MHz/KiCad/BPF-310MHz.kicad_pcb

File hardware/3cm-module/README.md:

# 3 cm Tracking Generator Module (9.5–11.5 GHz)

The 3 cm module is the harmonic‑mode RF upconversion stage of the Tracking Generator.  
It reconstructs the analyzer’s 9.5–11.5 GHz sweep by combining:

- the analyzer’s 1st LO (LO_SA = 4.905–5.905 GHz)  
- the analyzer’s internal IF = 310.7 MHz (harmonic 2 mode)  
- a TG‑generated IF_TG = 310.7 MHz from an ADF4351  
- a doubled version of the analyzer’s 1st LO (LO₂ = 9.81–11.81 GHz) for the HMC220 mixer

All frequencies remain coherent with the analyzer because they are derived from the analyzer’s 1st LO and 10 MHz reference.

## Harmonic‑mode coherence

In the 3 cm band, the HP 8562A/B uses **2× harmonic mixing** with an internal IF of **310.7 MHz**.

The analyzer’s 1st LO follows:  
`2 × LO_SA = RF_SA + 310.7 MHz`  →  `LO_SA = (RF_SA + 310.7 MHz) / 2`

For RF_SA = 9.5–11.5 GHz, this yields:  
`LO_SA = 4.905–5.905 GHz`

This is the actual LO range the 3 cm TG module must track.

## Why the LO must be doubled

The HMC220 mixer requires:

- IF port: DC–4 GHz  
- LO/RF ports: 5–12 GHz  

The analyzer’s 1st LO (4.905–5.905 GHz) is too low for the HMC220 LO port.  
Therefore, the TG uses a ×2 multipiler (HMC204): `LO₂ = 2 × LO_SA = 9.81–11.81 GHz`, fitting the mixer’s LO range.

## IF_TG generation (ADF4351)

The TG generates a fixed IF signal using the ADF4351: `IF_TG = 310.7 MHz`.  
The MCU programs the ADF4351 via SPI and maintains sweep coherence with the analyzer’s 10 MHz reference.
A Band Pass Filter at 310 MHz follows the ADF4351 to maintain signal purity. 

## Mixer output and TG coherence

The HMC220 mixer produces: `RF_TG = LO₂ – IF_TG = RF_SA`  
Substituting the ranges:  
LO₂ = 9.81–11.81 GHz, IF_TG = 310.7 MHz → RF_TG = 9.5–11.5 GHz.  
This exactly matches the analyzer’s displayed frequency.

## Module architecture and building blocks

### HMC204 Analyzer LO doubler
- Input: LO_SA = 4.905–5.905 GHz  
- Output: LO₂ = 9.81–11.81 GHz  
- Purpose: shift analzer LO into HMC220 LO range while maintaining sweep coherence

### ADF4351 IF_TG generator
- Output: 310.7 MHz (fixed)  
- MCU‑controlled and reference‑locked  
- Purpose: provide the IF offset needed to reconstruct RF_TG

**HFSS modeling results optimized for standard LC values:** 

### HMC220 mixer
- LO port: 9.81–11.81 GHz  
- IF port: 310.7 MHz  
- RF port: 9.5–11.5 GHz  
- Purpose: perform the upconversion that produces the 3 cm TG output

### Band‑pass filter (8–12 GHz)
- Removes LO₂ leakage, IF_TG leakage, and mixer images  
- Ensures only the 9.5–11.5 GHz band reaches the amplifier

Did not succeed yet in modeling a proper BPF so, for now a simple lowpass filter on 0.8mm FR4. 

**HFSS modeling results for a stepped impedance lowpass filter:** 

### RF gain stage + output pad
- Provides ~0 dBm output  
- Maintains linearity across the sweep  
- Ensures stable 50 Ω output at the TG output SMA connector

## Performance targets

### Frequency performance
- Output band: 9.5–11.5 GHz  
- Must track analyzer sweep exactly  
- Fast settling to follow analyzer sweep speed

### Amplitude performance
- Target output: ~0 dBm  
- Flatness corrected at system level  
- No compression across sweep

### Spectral purity
- Low LO₂ leakage  
- Low IF_TG leakage  
- Spurs dominated by ADF4351 + multiplier chain  
- Phase noise dominated by analyzer LO

### Implementation constraints
- RF layout suitable for >10 GHz  
- Isolation between LO₂, IF_TG, and RF paths

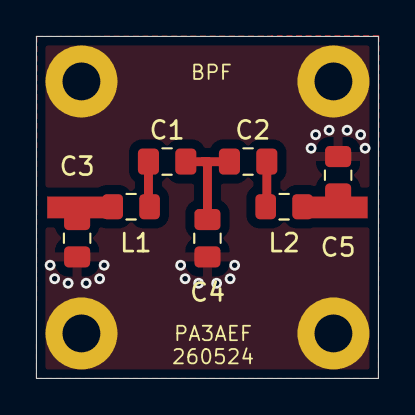
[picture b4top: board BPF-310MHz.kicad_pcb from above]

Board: 2 copper layers, 19.0 x 19.0 mm, 11 parts (0 on the bottom side), 6 nets.

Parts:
C1, C2: 15pF; C_0805_2012Metric_Pad1.18x1.45mm_HandSolder
C3, C5: 68pF; C_0805_2012Metric_Pad1.18x1.45mm_HandSolder
C4: 470pF; C_0805_2012Metric_Pad1.18x1.45mm_HandSolder
H1, H2, H3, H4: Hole_M2; MountingHole_2.1mm_M2_Pad
L1, L2: 22nH; L_0805_2012Metric_Pad1.15x1.40mm_HandSolder

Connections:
GND: C3.1, C4.1, C5.1, H1.1, H2.1, H3.1, H4.1
unnamed: C1.1, C2.2, C4.2
unnamed: C1.2, L1.2
unnamed: C2.1, L2.1
unnamed: C3.2, L1.1
unnamed: C5.2, L2.2

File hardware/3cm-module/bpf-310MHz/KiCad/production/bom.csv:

Designator,Footprint,Quantity,Value,LCSC Part #
"C1, C2",0805,2,15pF,
"C3, C5",0805,2,68pF,
C4,0805,1,470pF,
"L1, L2",0805,2,22nH,

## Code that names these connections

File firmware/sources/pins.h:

#ifndef PINS_H
#define PINS_H

// =========================================================
// SPI0 (hardware)
// =========================================================
constexpr int PIN_SCK  = 18;   // PIN 24 - SPI0 SCK
constexpr int PIN_MOSI = 19;   // PIN 25 - SPI0 MOSI
constexpr int PIN_MISO = 16;   // PIN 21 - SPI0 MISO (not used)

// =========================================================
// Ramp input (ADC0)
// =========================================================
constexpr int PIN_RAMP_ADC = 26;   // PIN 31 - ADC0

// =========================================================
// Rotary switch (Gray code)
// =========================================================
constexpr int PIN_ROT_A = 14;   // PIN 19
constexpr int PIN_ROT_B = 15;   // PIN 20

// =========================================================
// PE42540 LO switch (2-bit select)
// =========================================================
constexpr int PIN_PE_A = 20;    // PIN 26
constexpr int PIN_PE_B = 17;    // PIN 22

// =========================================================
// PE42540 LO switch (2-bit select)
// =========================================================
constexpr int PIN_REF_PRESENT = 21;   // PIN 27
constexpr int PIN_REF_PRESENT_N = 22; // PIN 29

// =========================================================
// Per band control pins
// Each band has: CS, CE, LD, RF_EN
// =========================================================

// ---- BANDBASE ----
constexpr int CS_BASE     = 27;  // PIN 32
constexpr int CE_BASE     = 28;  // PIN 34
constexpr int LD_BASE     = 0;  // PIN 1
constexpr int RFEN_BASE   = 1;  // PIN 2

// ---- 3 cm ----
constexpr int CS_3CM      = 6;  // PIN 9 
constexpr int CE_3CM      = 7;  // PIN 10
constexpr int LD_3CM      = 8;  // PIN 11
constexpr int RFEN_3CM    = 9;  // PIN 12

// ---- 6 cm ----
constexpr int CS_6CM      = 2;   // PIN 4
constexpr int CE_6CM      = 3;   // PIN 5
constexpr int LD_6CM      = 4;   // PIN 6
constexpr int RFEN_6CM    = 5;   // PIN 7

// ---- 15 mm ----
constexpr int CS_12MM     = 10;   // PIN 14
constexpr int CE_12MM     = 11;   // PIN 15
constexpr int LD_12MM     = 12;   // PIN 16
constexpr int RFEN_12MM   = 13;   // PIN 17

#endif

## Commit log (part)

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2026-05-07 Add system architecture diagram
2026-05-07 Update block diagram reference in system architecture documentation
2026-05-07 Replace block diagram reference with an embedded image in system architecture documentation
2026-05-07 Update project title to indicate work in progress status
2026-05-09 Refactor code structure for improved readability and maintainability
2026-05-11 Update LO architecture and RF SA-LO distribution documentation; add firmware architecture overview
2026-05-11 Refactor README.md for improved clarity and consistency in the 3 cm Tracking Generator module description
2026-05-11 Refactor README.md to enhance clarity and detail in the Base‑Band Tracking Generator module description
2026-05-11 Remove detailed documentation for the 6 cm Module from README.md
2026-05-11 Refactor documentation for clarity and consistency in LO architecture and Base-Band module descriptions
2026-05-11 Refactor README.md and add documentation for Analyzer LO Internals to enhance clarity and detail
2026-05-15 Refactor documentation for clarity and consistency across various modules, including updates to the 3 cm Tracking Generator, Base-Band module, and Analyzer LO Internals. Enhance details on LO generat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
2026-05-15 Update README.md to clarify status of Base-Band and 3 cm modules, noting proof of concept testing and successful tracking at 10 GHz with 2 GHz span.
2026-05-16 Refactor architecture documentation for Tracking Generator modules
    - Deleted obsolete files:
    - 04-baseband-module.md
    - 05-3cm-module.md
    - 06-analyser-lo-internals.md
    - Added new files for updated architecture:
    - 03-analyser-lo-internals.md: Detailed explanation of the analyzer's LO generation.
2026-05-17 typos
2026-05-17 Update LO_SA range details for 6 cm and 3 cm bands in LO architecture documentation
2026-05-17 Update 6cm, 3cm, and 15mm module documentation for accuracy and clarity
2026-06-29 Add files via upload
    Repo rebuild
2026-06-30 Update README.md to clarify LO Module description in hardware section
2026-06-30 Add mechanical and usage documentation folders to README
